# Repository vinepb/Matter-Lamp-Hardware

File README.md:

# Lamp Controller with Matter

## Overview

This project is a smart lamp controller designed for a 3V3 3D printed lamp. It utilizes an ESP32 microcontroller and integrates seamlessly with Apple's HomeKit ecosystem. The project consists of both software and hardware components, making it a complete solution for controlling the lamp remotely.

## Software

Refer to [Matter-Lamp-Firmware](https://github.com/vinepb/Matter-Lamp-Firmware).

## Hardware

The hardware component of ths project was designed using [KiCad](https://www.kicad.org) and includes a schematic and a PCB layout.

### PCB Layout

### List of Materials

| Component           | Quantity | Footprint                                        |
|---------------------|----------|--------------------------------------------------|
| Resistor 10k Ohm    | 1        | Resistor_THT:R_Axial_DIN0207_L6.3mm_D2.5mm_P10.16mm_Horizontal |
| Resistor 300 Ohm    | 3        | Resistor_THT:R_Axial_DIN0207_L6.3mm_D2.5mm_P10.16mm_Horizontal |
| Transistor 2N3906   | 1        | Package_TO_SOT_THT:TO-92_Inline                |
| Capacitor 10uF      | 3        | Capacitor_THT:C_Radial_D5.0mm_H11.0mm_P2.00mm |
| Regulator LM1117T 3V3 | 1      | Package_TO_SOT_THT:TO-220-3_Horizontal_TabDown |
| Regulator LM1117T 5V | 1       | Package_TO_SOT_THT:TO-220-3_Horizontal_TabDown |
| ESP32-WROOM-32      | 1        | DEVKIT V1                                        |
| Jack P4 Female      | 1        | Connector_BarrelJack:BarrelJack_Horizontal_3pin |
| 15x Pin Socket       | 2        | 2.54mm vertical                                  |
| Lamp Connector      | 1        | Connector_AMASS_XT30U-F_1x02_P5.0mm_Vertical  |
| 1m Red AWG 20 Cable   | 1        | -                                                |
| 1m Black AWG 20 Cable | 1        | -                                                |
| 9VDC P4 Power Supply  | 1        | -                                                |

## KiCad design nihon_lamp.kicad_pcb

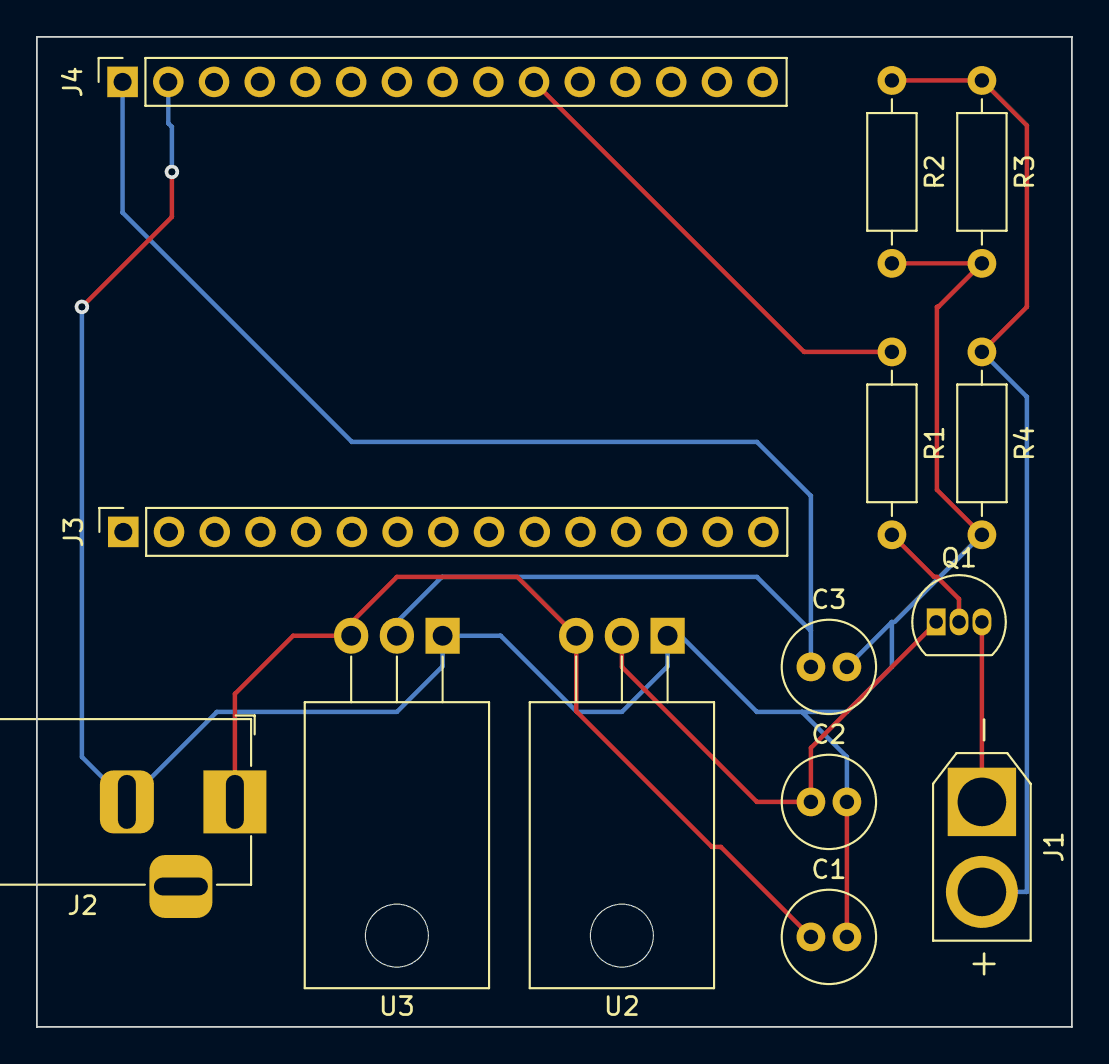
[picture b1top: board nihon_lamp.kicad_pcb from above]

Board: 2 copper layers, 57.5 x 55.0 mm, 14 parts (0 on the bottom side), 8 nets.

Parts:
C1, C2, C3: C; C_Radial_D5.0mm_H11.0mm_P2.00mm
J1: Lamp LED; AMASS_XT30U-F_1x02_P5.0mm_Vertical
J2: Barrel_Jack_MountingPin; BarrelJack_Horizontal
J3, J4: Conn_01x15_Pin; PinSocket_1x15_P2.54mm_Vertical
Q1: 2N3906; TO-92_Inline
R1: 10k; R_Axial_DIN0207_L6.3mm_D2.5mm_P10.16mm_Horizontal
R2, R3, R4: 300; R_Axial_DIN0207_L6.3mm_D2.5mm_P10.16mm_Horizontal
U2: LM1117T-3.3; TO-220-3_Horizontal_TabDown
U3: LM1117T-5.0; TO-220-3_Horizontal_TabDown

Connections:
+3V3: C2.1, Q1.1 (E), U2.2 (VO)
+5V: C3.1, J4.1, U3.2 (VO)
+9V: C1.1, J2.1, U2.3 (VI), U3.3 (VI)
GND: C1.2, C2.2, C3.2, J2.2, J4.2, R2.2, R3.2, R4.2, U2.1 (GND), U3.1 (GND)
unnamed: J1.1, Q1.3 (C)
unnamed: J1.2, R2.1, R3.1, R4.1
unnamed: J4.10, R1.1
unnamed: Q1.2 (B), R1.2
